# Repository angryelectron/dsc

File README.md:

The DSC is an Arduino-based differential solar controller.  Please visit
http://angryelectron.com/projects/dsc for more information.

Here you will find Eagle project files for the schematic and PCB, the DSC
firmware (Arduino sketch), a Google Gadget, and some Bash scripts that can be
used for monitoring.

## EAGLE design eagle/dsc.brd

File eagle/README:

This is a CadSoft Eagle project for the DSC schematic capture and PCB layout. 

Set your Eagle project directory to this one for easy access to projects,
libraries, scripts, and design rules within the Eagle IDE.

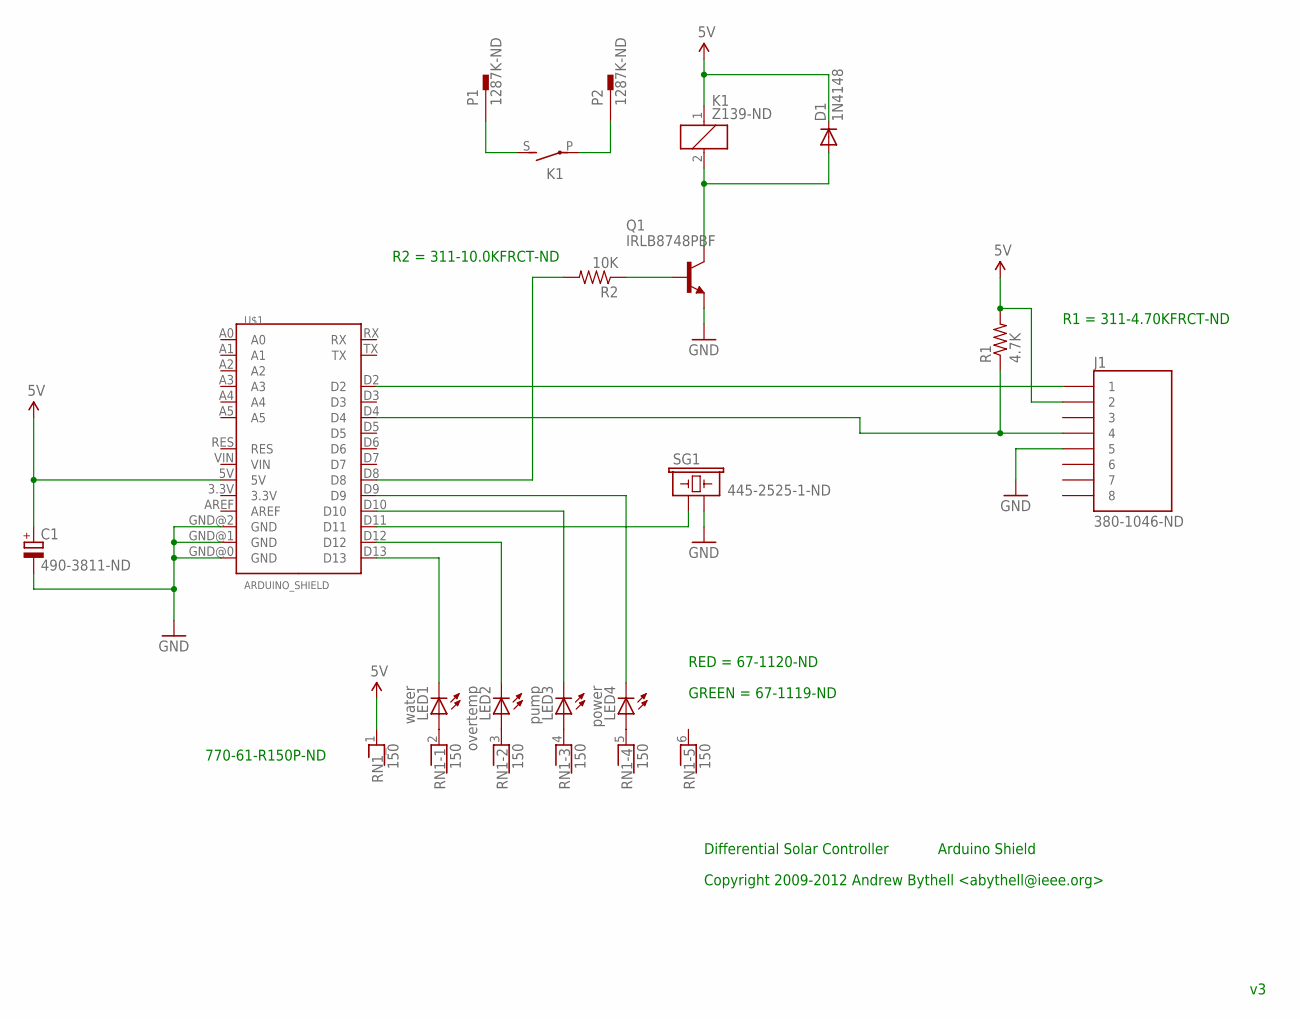
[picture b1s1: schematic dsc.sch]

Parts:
C1: 490-3811-ND; E3,5-8
D1: 1N4148; DO35-10
J1: 380-1046-ND; RJ45-8
K1: Z139-ND; G2RA
LED1: water; LED5MM
LED2: overtemp; LED5MM
LED3: pump; LED5MM
LED4: power; LED5MM
P1, P2: 1287K-ND; F061.100
Q1: IRLB8748PBF; TO18
R1: 4.7K; 1206
R2: 10K; 1206
RN1: 150; RN-6
SG1: 445-2525-1-ND; BUZZER-12MM-AB
U$1: ARDUINO_SHIELD; DUEMILANOVE_SHIELD

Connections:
5V: C1.+, D1.C, J1.2, K1.1, R1.2, RN1.1, U$1.5V
ERASE: J1.4, R1.1, U$1.D4
GND: C1.-, J1.5, Q1.1 (E), SG1.- (2), U$1.GND@0 (GND), U$1.GND@1 (GND), U$1.GND@2 (GND)
unnamed: Q1.2 (B), R2.1
unnamed: R2.2, U$1.D8
unnamed: D1.A, K1.2, Q1.3 (C)
unnamed: LED1.A, RN1.2
unnamed: LED2.A, RN1.3
unnamed: LED3.A, RN1.4
unnamed: LED4.A, RN1.5
unnamed: LED1.K (C), U$1.D13
unnamed: LED2.K (C), U$1.D12
unnamed: LED3.K (C), U$1.D10
unnamed: LED4.K (C), U$1.D9
unnamed: SG1.+ (1), U$1.D11
unnamed: K1.S, P1.A1, P1.A2
unnamed: K1.P, P2.A1, P2.A2
unnamed: J1.1, U$1.D2

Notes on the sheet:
Differential Solar Controller
Arduino Shield
770-61-R150P-ND
RED = 67-1120-ND
GREEN = 67-1119-ND
R1 = 311-4.70KFRCT-ND
R2 = 311-10.0KFRCT-ND
Copyright 2009-2012 Andrew Bythell <abythell@ieee.org>

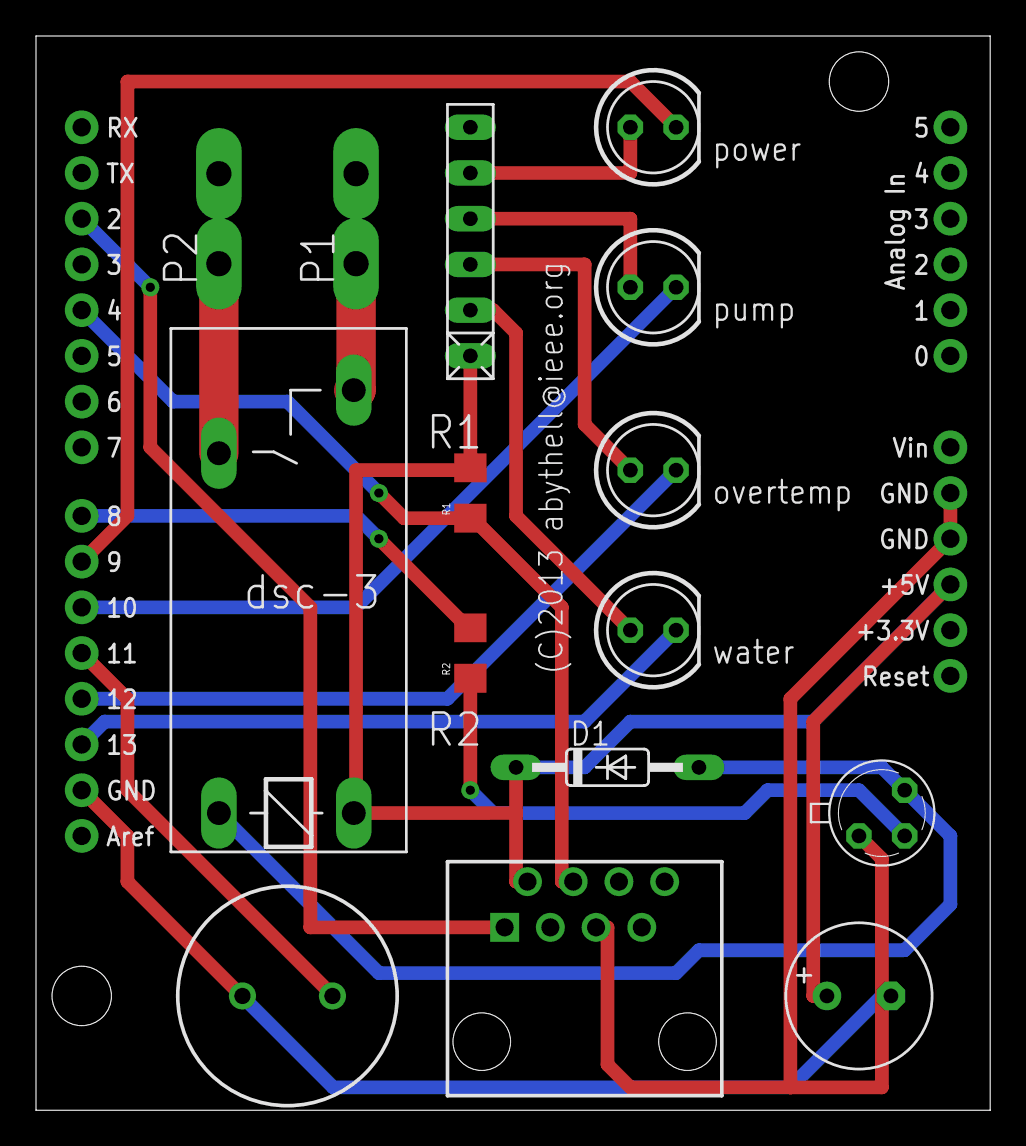
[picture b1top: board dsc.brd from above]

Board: 2 copper layers, 53.0 x 59.7 mm, 16 parts (0 on the bottom side), 18 nets.

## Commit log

2013-01-03 initial import
2013-01-03 added GPL
2013-01-03 Replaced quickfit terminals with updated part - old part was causing DRC errors. Project updated for Eagle 6.3.
